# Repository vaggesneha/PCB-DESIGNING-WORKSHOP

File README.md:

# PCB-DESIGNING-WORKSHOP
2-DAY "Exploring the Art of PCB Designing"

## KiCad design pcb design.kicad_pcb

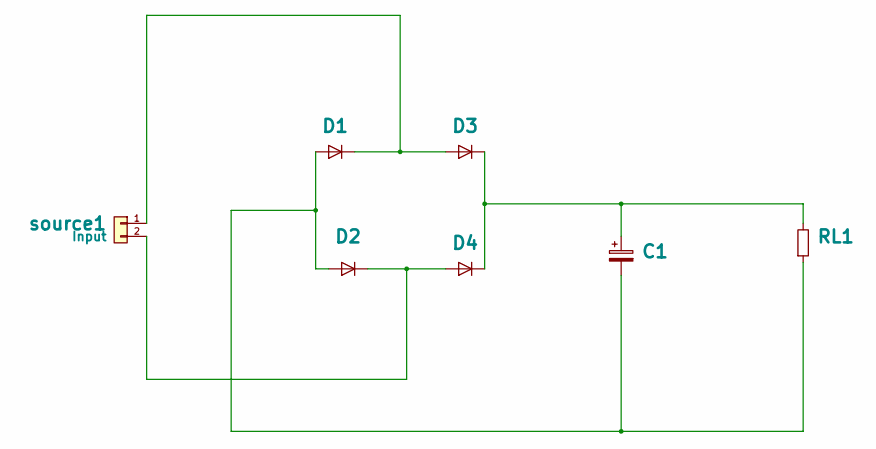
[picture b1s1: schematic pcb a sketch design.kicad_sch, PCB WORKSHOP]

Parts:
C1: C_Polarized; CP_Radial_D4.0mm_P2.00mm
D1, D2, D3, D4: D; D_A-405_P2.54mm_Vertical_AnodeUp
RL1: R; R_Axial_DIN0204_L3.6mm_D1.6mm_P5.08mm_Vertical
source1: Input; PinSocket_1x02_P2.00mm_Vertical

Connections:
unnamed: C1.2, D1.2 (A), D2.2 (A), RL1.2
unnamed: D1.1 (K), D3.2 (A), source1.1
unnamed: D2.1 (K), D4.2 (A), source1.2
unnamed: C1.1, D3.1 (K), D4.1 (K), RL1.1

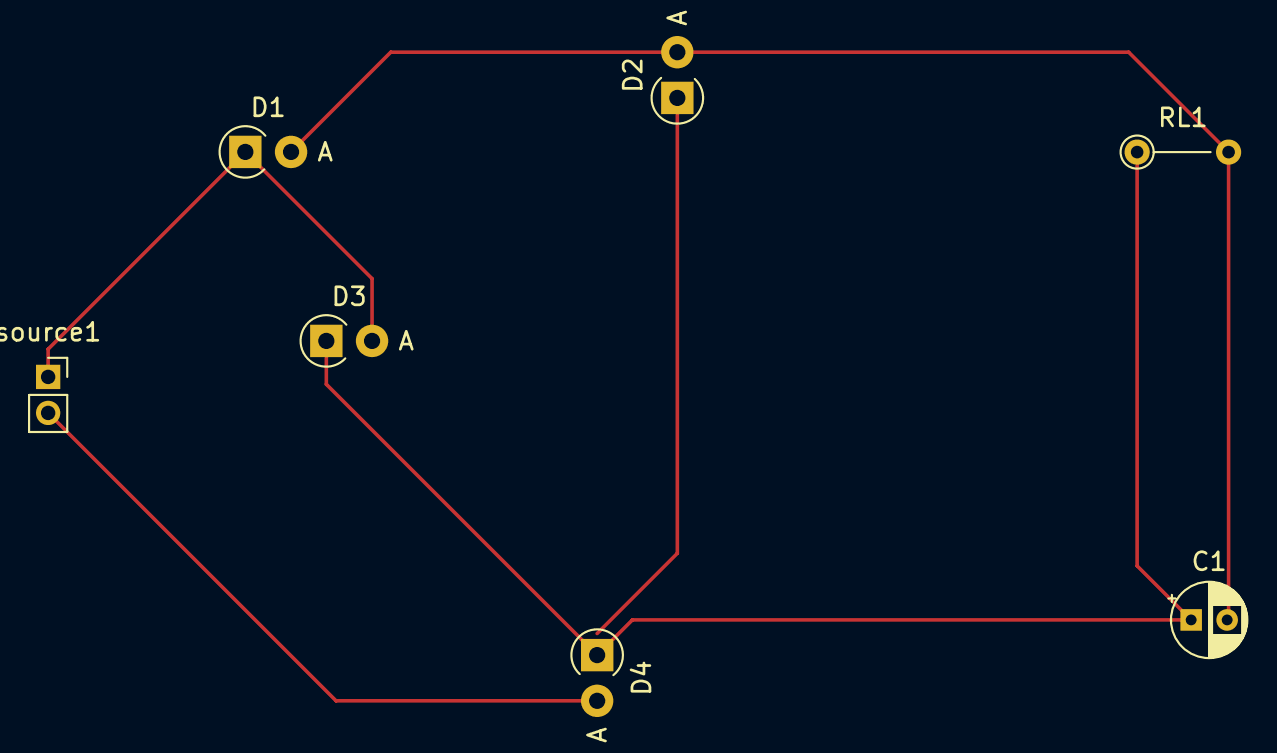
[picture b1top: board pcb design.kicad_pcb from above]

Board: 2 copper layers, 7 parts (0 on the bottom side), 4 nets.

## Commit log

2024-07-20 Add files via upload
    PCB-Printed Circuit Boards is known for mechanically supported and electrically connect electronic components using CONDUCTIVE pathways, tracks or signal traces ETCHED from COPPER sheets laminated on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
